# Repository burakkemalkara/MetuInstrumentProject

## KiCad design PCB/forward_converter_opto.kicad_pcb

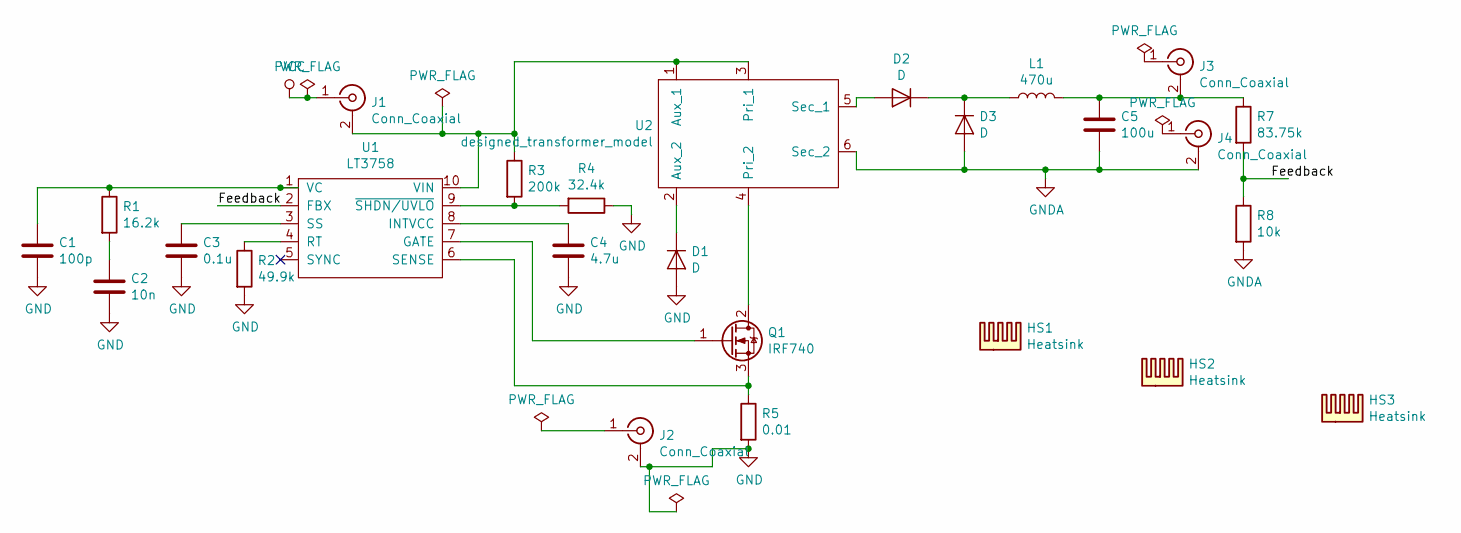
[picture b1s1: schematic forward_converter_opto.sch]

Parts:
C1: 100p; CP_Radial_D10.0mm_P5.00mm
C2: 10n; CP_Radial_D10.0mm_P5.00mm
C3: 0.1u; CP_Radial_D10.0mm_P5.00mm
C4: 4.7u; CP_Radial_D10.0mm_P5.00mm
C5: 100u; CP_Radial_D10.0mm_P5.00mm
D1, D2, D3: D; TO-220-2_Vertical
HS1, HS2, HS3: Heatsink; heatsink
J1, J2, J3, J4: Conn_Coaxial; BNC_PanelMountable_Vertical
L1: 470u; fw_inductor
Q1: IRF740; TO-220-3_Vertical
R1: 16.2k; R_Axial_DIN0207_L6.3mm_D2.5mm_P10.16mm_Horizontal
R2: 49.9k; R_Axial_DIN0207_L6.3mm_D2.5mm_P10.16mm_Horizontal
R3: 200k; R_Axial_DIN0207_L6.3mm_D2.5mm_P10.16mm_Horizontal
R4: 32.4k; R_Axial_DIN0207_L6.3mm_D2.5mm_P10.16mm_Horizontal
R5: 0.01; R_Axial_DIN0207_L6.3mm_D2.5mm_P10.16mm_Horizontal
R7: 83.75k; R_Axial_DIN0207_L6.3mm_D2.5mm_P10.16mm_Horizontal
R8: 10k; R_Axial_DIN0207_L6.3mm_D2.5mm_P10.16mm_Horizontal
U1: LT3758; MSOP-10_3x3mm_P0.5mm
U2: designed_transformer_model; forward_converter_transformer

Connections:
/Feedback: R7.2, R8.1, U1.2 (FBX)
GND: C1.2, C2.2, C3.2, C4.2, D1.2 (A), J2.2 (Ext), R2.2, R4.1, R5.2
GNDA: C5.2, D3.2 (A), J4.2 (Ext), R8.2, U2.6 (Sec_2)
unnamed: C1.1, R1.1, U1.1 (VC)
unnamed: C2.1, R1.2
unnamed: C3.1, U1.3 (SS)
unnamed: C4.1, U1.8 (INTVCC)
unnamed: C5.1, J3.2 (Ext), L1.2, R7.1
unnamed: D1.1 (K), U2.2 (Aux_2)
unnamed: D2.1 (K), D3.1 (K), L1.1
unnamed: D2.2 (A), U2.5 (Sec_1)
unnamed: J1.2 (Ext), R3.1, U1.10 (VIN), U2.1 (Aux_1), U2.3 (Pri_1)
unnamed: Q1.1 (G), U1.7 (GATE)
unnamed: Q1.2 (D), U2.4 (Pri_2)
unnamed: Q1.3 (S), R5.1, U1.6 (SENSE)
unnamed: R2.1, U1.4 (RT)
unnamed: R3.2, R4.2, U1.9 (~SHDN/UVLO)
VCC: J1.1 (In)

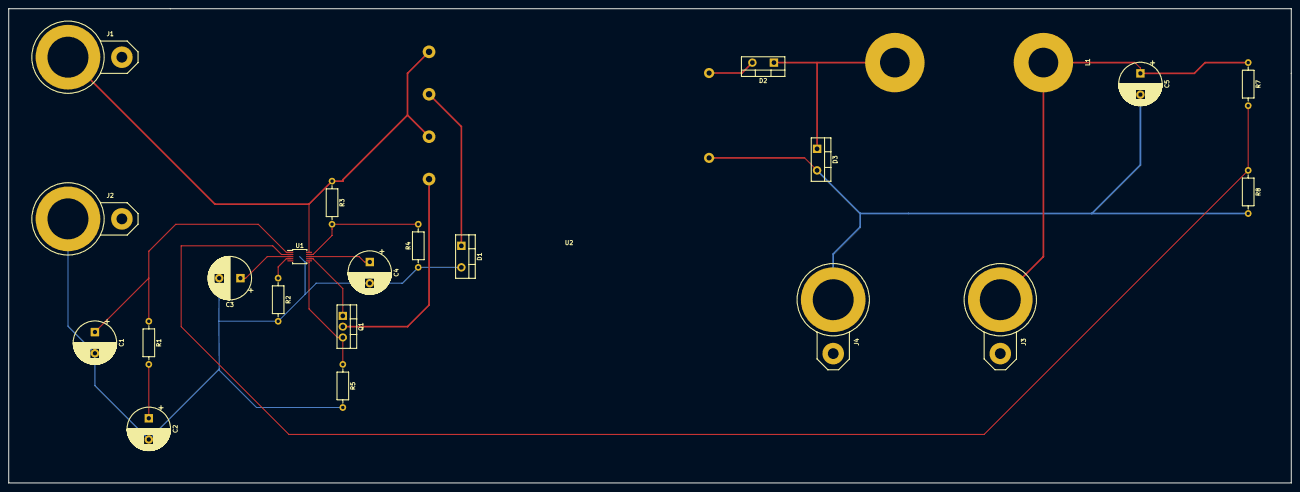
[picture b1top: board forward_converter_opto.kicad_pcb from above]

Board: 2 copper layers, 302.3 x 111.8 mm, 26 parts (0 on the bottom side), 17 nets.

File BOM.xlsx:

Reference | Quantity | Value | Footprint | Datasheet | Unit Price ($) | Total Price ($)
C1 | 1 | 100p | Capacitor_THT:CP_Radial_D10.0mm_P5.00mm | ~ | 0.04 | 0.04
C2 | 1 | 10n | Capacitor_THT:CP_Radial_D10.0mm_P5.00mm | ~ | 0.04 | 0.04
C3 | 1 | 0.1u | Capacitor_THT:CP_Radial_D10.0mm_P5.00mm | ~ | 0.04 | 0.04
C4 | 1 | 4.7u | Capacitor_THT:CP_Radial_D10.0mm_P5.00mm | ~ | 0.04 | 0.04
C5 | 1 | 100u | Capacitor_THT:CP_Radial_D10.0mm_P5.00mm | ~ | 0.45 | 0.45
D1 D2 D3 | 3 | D | Package_TO_SOT_THT:TO-220-2_Vertical | ~ | 1.07 | 3.21
J1 J2 J3 J4 | 4 | Conn_Coaxial | Connector_Coaxial:BNC_PanelMountable_Vertical | ~ | 0.2 | 0.8
L1 | 1 | 470u | forward_converter:fw_inductor | ~ | 12.4 | 12.4
Q1 | 1 | IRFB4127PBF | Package_TO_SOT_THT:TO-220-3_Vertical | http://www.vishay.com/docs/91054/91054.pdf | 2.98 | 2.98
R1 | 1 | 16.2k | Resistor_THT:R_Axial_DIN0207_L6.3mm_D2.5mm_P10.16mm_Horizontal | ~ | 0.01 | 0.01
R2 | 1 | 49.9k | Resistor_THT:R_Axial_DIN0207_L6.3mm_D2.5mm_P10.16mm_Horizontal | ~ | 0.01 | 0.01
R3 | 1 | 200k | Resistor_THT:R_Axial_DIN0207_L6.3mm_D2.5mm_P10.16mm_Horizontal | ~ | 0.01 | 0.01
R4 | 1 | 32.4k | Resistor_THT:R_Axial_DIN0207_L6.3mm_D2.5mm_P10.16mm_Horizontal | ~ | 0.01 | 0.01
R5 | 1 | 0.01 | Resistor_THT:R_Axial_DIN0207_L6.3mm_D2.5mm_P10.16mm_Horizontal | ~ | 0.01 | 0.01
R7 | 1 | 83.75k | Resistor_THT:R_Axial_DIN0207_L6.3mm_D2.5mm_P10.16mm_Horizontal | ~ | 0.01 | 0.01
R8 | 1 | 10k | Resistor_THT:R_Axial_DIN0207_L6.3mm_D2.5mm_P10.16mm_Horizontal | ~ | 0.01 | 0.01
U1 | 1 | LT3758 | Package_SO:MSOP-10_3x3mm_P0.5mm |  | 5.92 | 5.92
U2 | 1 | designed_transformer_model | forward_converter:forward_converter_transformer |  | 10 | 10
Total Price($) |  |  |  |  |  | 35.990000000000009

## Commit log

2020-03-21 Simulation results with core loss calculation
2020-03-22 report template
2020-03-23 core consideration
2020-03-23 Mosfet Consideration
2020-03-23 Power clacultions are done, few things to complete
2020-03-23 All report finished
2020-03-31 final fixes
2020-06-20 LTspice controller
2020-06-23 Sİmulation corrections
2020-06-23 Add files via upload
    PCB schematic, and footprints completed
2020-06-23 Transfer Function
2020-06-24 Tranfer function and calculations are completed
2020-06-24 Controller calculations completed and new mosfet selected
2020-06-24 Add files via upload
    PCB design is completed except thickness and width adjustments of connections
2020-06-24 Add files via upload
    PCB design is completed, ground plane added, width of layers adjusted,
    3D images of designed PCB is added
2020-06-24 Simulation minor corrections
2020-06-24 Simulation details explained at report
2020-06-24 Add files via upload
    Gerber Files and BOM added
    Final Design of our PCB
    Note that forward_converter_opto files are designed PCB
2020-06-24 Add files via upload
    Bill of Materials (BOM)
2020-06-24 Project completely finished
2020-06-24 Report changed
